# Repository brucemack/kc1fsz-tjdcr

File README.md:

Overview
========

This is my compact PCB implementation of the famous Thomas Jefferson Direct Conversion Receiver
designed by Bill Meara (N2CQR) and Dean Souleles (KK4DAS). Full documentation for the 
original rig [can be found here](https://hackaday.io/project/190327-high-schoolers-build-a-radio-receiver). This project has been discussed at length
on the excellent Solder Smoke Podcast and in a detailed series of videos that can be found
[starting here](https://www.youtube.com/watch?v=rLjxU2rMeXw). I would particularly 
encourage you to watch Dean's superb tutorial series on YouTube. 

I built this rig as part of the "Direct Conversion Challenge" issued by Bill and Dean. As
stipulated by Bill/Dean, I am resisting all temptations to modify/improve the original 
circuit. However, technically speaking this is not a *pure* TJDCR since there 
are a few departures from the recommended construction techniques and part selections. 
Importantly, I am using modern construction techniques including a commercial PCB (single board), SMD 
components (mostly 0805), and the most compact layout I could come up with. My KiCad model is provided
here for anyone who wants to experiment with it.

A huge thanks to Scott KQ4AOP for creating and sending me the tuning form 
needed to build the PTO! You also need a brass 1/4-20 bolt around 2.5" long and two 1/4-20 nuts.

Here's a demo video of the working rig:

Here's the KiCad rendering of my board.  The part reference numbers are correct
in this picture:

Here's what the raw PCB it looks like in real life. *The part reference numbers didn't 
match Bill/Dean's schematic in this version of the board* so don't get confused.  The KiCad model was later updated 
to fix this and the 2025-03 board has the correct reference numbers.

Here's the populated board:

And the full rig:

> [!IMPORTANT]  
> I know the purists may raise objections, so I would like to emphasize the value
> of building the TJDCR rig from Bill/Dean's exact specifications *first* before getting into 
> modifications including (but not limited to) PCBs and SMDs. The main point of the TJDCR
> project is to learn the process of building from scratch, and using a commercially
> fabricated PCB
> somewhat defeats that purpose. I've built DCR rigs a few times (as well as several SSB transceivers) using traditional Manhattan/Ugly (aka Beauty) 
> style so I'm trying to do something a bit different for fun. That being said, we are 
> moving into a new world where many components of value to radio homebrewers are not 
> available in through-hole packages. I would encourage everyone get over their
> fears of surface-mount parts, buy a decent headband magnifier, and start practicing 
> SMD-homebrew. I've found that by modifying the stock IPC-7351 0805 footprints provided in
> KiCad to 
> extend the pads outward 0.5mm or so you can use a normal soldering iron with a fine tip with 
> no problems.

Once the testing is complete I will make the PCB/BOM available for anyone who wants
to try building it in this style.

My [KiCAD schematic is here](https://github.com/brucemack/kc1fsz-tjdcr/blob/main/hw/tjdcr-1/plots/tjdcr-1.pdf) if you want to have a look. I've tried to use the official TJDCR part reference numbers
as much as possible.

Modification Notes
==================

This will probably get me into trouble, but I've deviated in a few places. I believe 
I've maintained the spirit of the original circuit. :grin:

* This is a single board design, whereas Bill/Dean recommend 4 boards to promote modularity.
You will note that I've silk-screened borders around the 4 modules on my board to 
emphasize the modularity of the original design. I have included test points on the 
PCB and I assemble/test the circuit in the recommended modules to simplify debug.
* I'm using ceramic non-polarized capacitors in some places where Bill/Dean used
polarized electrolytic caps.
* I'm not using the recommended silver/mica caps in my oscillator, primarily because
of size constraints. The first iteration of the build used NP0 caps and stability looked
pretty good. I strongly suspect that the compact "hardened" PCB eliminates some of the variability 
experienced in the Manhattan/Ugly construction so oscillator stability may be less of an 
issue. I'm doing some more experiments and will provide a write-up on my findings later.
* I am using T37-6/FT37-43 toroids where Bill/Dean used T50-6/FT50-43. This requires 
thinner wire and a great deal of winding patience. I think the board can physically handle the T50s 
if necessary. 
* I did not put in a trimmer for the top coupling capacitor in the band-pass filter. I'm 
comfortable with a cut-and-try approach on that component given how it impacts the shape
of the filter. Trimmers on the shunt caps are critical given the variability in the 
toroidal inductors.
* I am using Schottky diodes in the mixer since those were in the original TJDCR rig. I noticed
a later change to the 1N4148 switching diode, but I have not made that change yet.
* Note the "LO Option" connector on the board, which is not in the original 
schematic.  Normally the two pins on this connector
should be jumpered together, but those wanting to inject external VFOs may want to 
open this connection and attach the external frequency source to pin 1. This 
is also a good place to connect a frequency counter or to bridge the VFO to the 
companion transmitter module.
* There are a few extra parts (C40-C41, R40-R41) in the schematic to support a frequency offset 
feature that is described in SSDRA (page 218 figure 4). This is used to drive 
a companion CW transmitter module. Don't plug in C40 when you 
are building the stock TJDCR.

Layout Notes
============

* The space under the frequency-determining components of the VFO has been
cleared on all layers. I've read in a few places that this improves VFO 
stability by removing the large (temperature-variable) capacitor that is 
formed between the PCB copper layers.
* Via fencing is used throughout the board to isolate the VFO and the audio
amplifier from everything else.
* THe power/ground connections are intentionally placed close to the power
stage of the audio amplifier to keep these relatively large currents away
from the earlier stages.

Tools
=====

I am using KiCAD V9 for the schematic capture and PCB layout.

Current Areas of Experimentation
================================

* The first iteration used a 4-layer PCB stackup since that provides the best
RF performance. As it turns out, there is very little routed on the bottom layer and 
the +9V routing is pretty simple. Plus, at 7 MHz a lot of this probably doesn't matter. I am 
going to create a 2-layer version of the layout to shave a 
few dollars and see if this makes any measurable difference. The 4-layer boards cost $1.40
each so we're not talking about a big difference here. 2-layer boards are also more easily
made by the fabs in the US. Unfortunately, I've not found an onshore fab that can do 4 layers as
quickly/cheaply as the offshore providers, which brings up a number of geopolitical issues. (Side
note: Thomas Jefferson was a strident global free-trade advocate.)
* The initial form-factor uses what I call a "half PCB": 100mm x 35mm.
That's half of the 100mm x 70mm size that cheap copper-clad PCB stock usually comes in.
I'm thinking of reworking the layout a bit to get into the more squarish 90mm x 50mm form-factor 
that is needed to fit into a Peppermint Altoids tin. Major QRP street cred possible here.
* I also like the super-small binocular BN43-2402 ferrite cores and will be testing
those on the mixer stage in the next iteration.
* I have a companion CW transmitter module I call "James Madison" which I will 
document later.

Bill Of Materials (2025-03 Version)
===================================

This parts list is provided for informational purposes. I didn't provide part numbers for a lot of the
generic components because I have a collection of those on hand. I like the 0805 SMD resistor and 
capacitor "books" since they contain anything you could ever want. The more unique parts can be
ordered from [DigiKey](http://www.digikey.com) using the part numbers provided. The audio transformer is a Mouser-only part.
The 2.54mm headers are cut from a long header strip.

This parts list follows the Bill/Dean component reference numbering scheme.

| Reference	| Value	| Notes |
| --------- | ----- | ----- |
| C1,C2 | 660p | NP0 Ceramic 0805 |
| C3 | 130p | NP0 Ceramic 0805 |
| C4,C5,C6,C7,C21,C41 | 0.1u | Generic Ceramic 0805 |
| C8,C14 | 10u | Generic Ceramic 0805 |
| C9,C11,C13 | 470u 10V | Tantalum in 7343 package, polarized (EX: Kyocera TPSE477K010R0100) |
| C10,C12,C15 | 47u | Generic Ceramic 0805 |
| C16 | 0.47u | Generic Ceramic 0805 |
| C17 | 33u | Generic Ceramic 0805 |
| C18,C19 | 150p | NP0 Ceramic 0805 |
| C20 | 10p | NP0 Ceramic 0805 |
| C40,C181,C191 | 6.5-30pF Trimmer | Manufacturer package (EX: EW Electronics GKG30086-05) |
| D1 | 8.2V 250mW Zener | SOT23-3 package (EX: onsemi BZX84C8V2LT1G) |
| D25,D34 | Schottky Diode Array | Pay attention to polarity, SOT23-3 package (EX: Diotec Semi BAT54S) |
| J1 | Antenna (50 ohms) | SMA connector female through-hole (EX: Amphenol 901-144-8RFX) |
| J2 | Tuning | Generic 2.54mm header |
| J3 | Power | Generic 2.54mm header | 
| J4 | LO Option | Generic 2.54mm header |
| J5 | Volume | Generic 2.54mm header |
| J6 | Speaker | Generic 2.54mm header |
| J7 | TX Offset | Generic 2.54mm header |
| L2 | 10u | 0805 package (EX: Taiyo Yuden LBR2012T100K) |
| L11 | 100u | 0805 package (EX: TDK MLZ2012N101LT000) |
| Q1,Q3,Q5,Q40 | NPN Transistor 3904 | SOT23-3 package (EX: onsemi MMBT3904LT1G) |
| Q2 | JFET Transistor J310 | SOT23-3 package (EX: onsemi SMMBFJ310LT3G) |
| Q4 | NPN Transistor 3904 | Generic TO-92 package |
| R1,R2 | 10k | Generic 0805 |
| R3 | 3.3k | Generic 0805 |
| R4,R6,R14 | 100R | Generic 0805 |
| R5 | 100k | Generic 0805 |
| R7 | 47R |	Generic 0805 |
| R8,R12,R16 | 14.7k | Generic 0805 |
| R9,R13,R17 | 4.7k | Generic 0805 |
| R10,R18 | 1k | Generic 0805 |
| R11,R19 | 470R | Generic 0805 |
| R20 | 220R | Generic 0805 |
| R40 | 47k | Generic 0805 |
| R41 | 2.2k | Generic 0805 |
| T1 | 5:28 Toroid transformer | Wound on T37-6 toroid, #28 wire |
| T2 | 5:28 Toroid transformer | Wound on T37-6 toroid, #28 wire |
| T3 | 1:1:1 Toroid transformer (trifilar) | Wound on FT37-43 toroid, #28 wire |
| T4 | 1:1:1 Toroid transformer (trifilar) | Wound on FT37-43 toroid, #28 wire |
| T5 | 8R:1k audio transformer| EX: Mouser 42TL013-RC |

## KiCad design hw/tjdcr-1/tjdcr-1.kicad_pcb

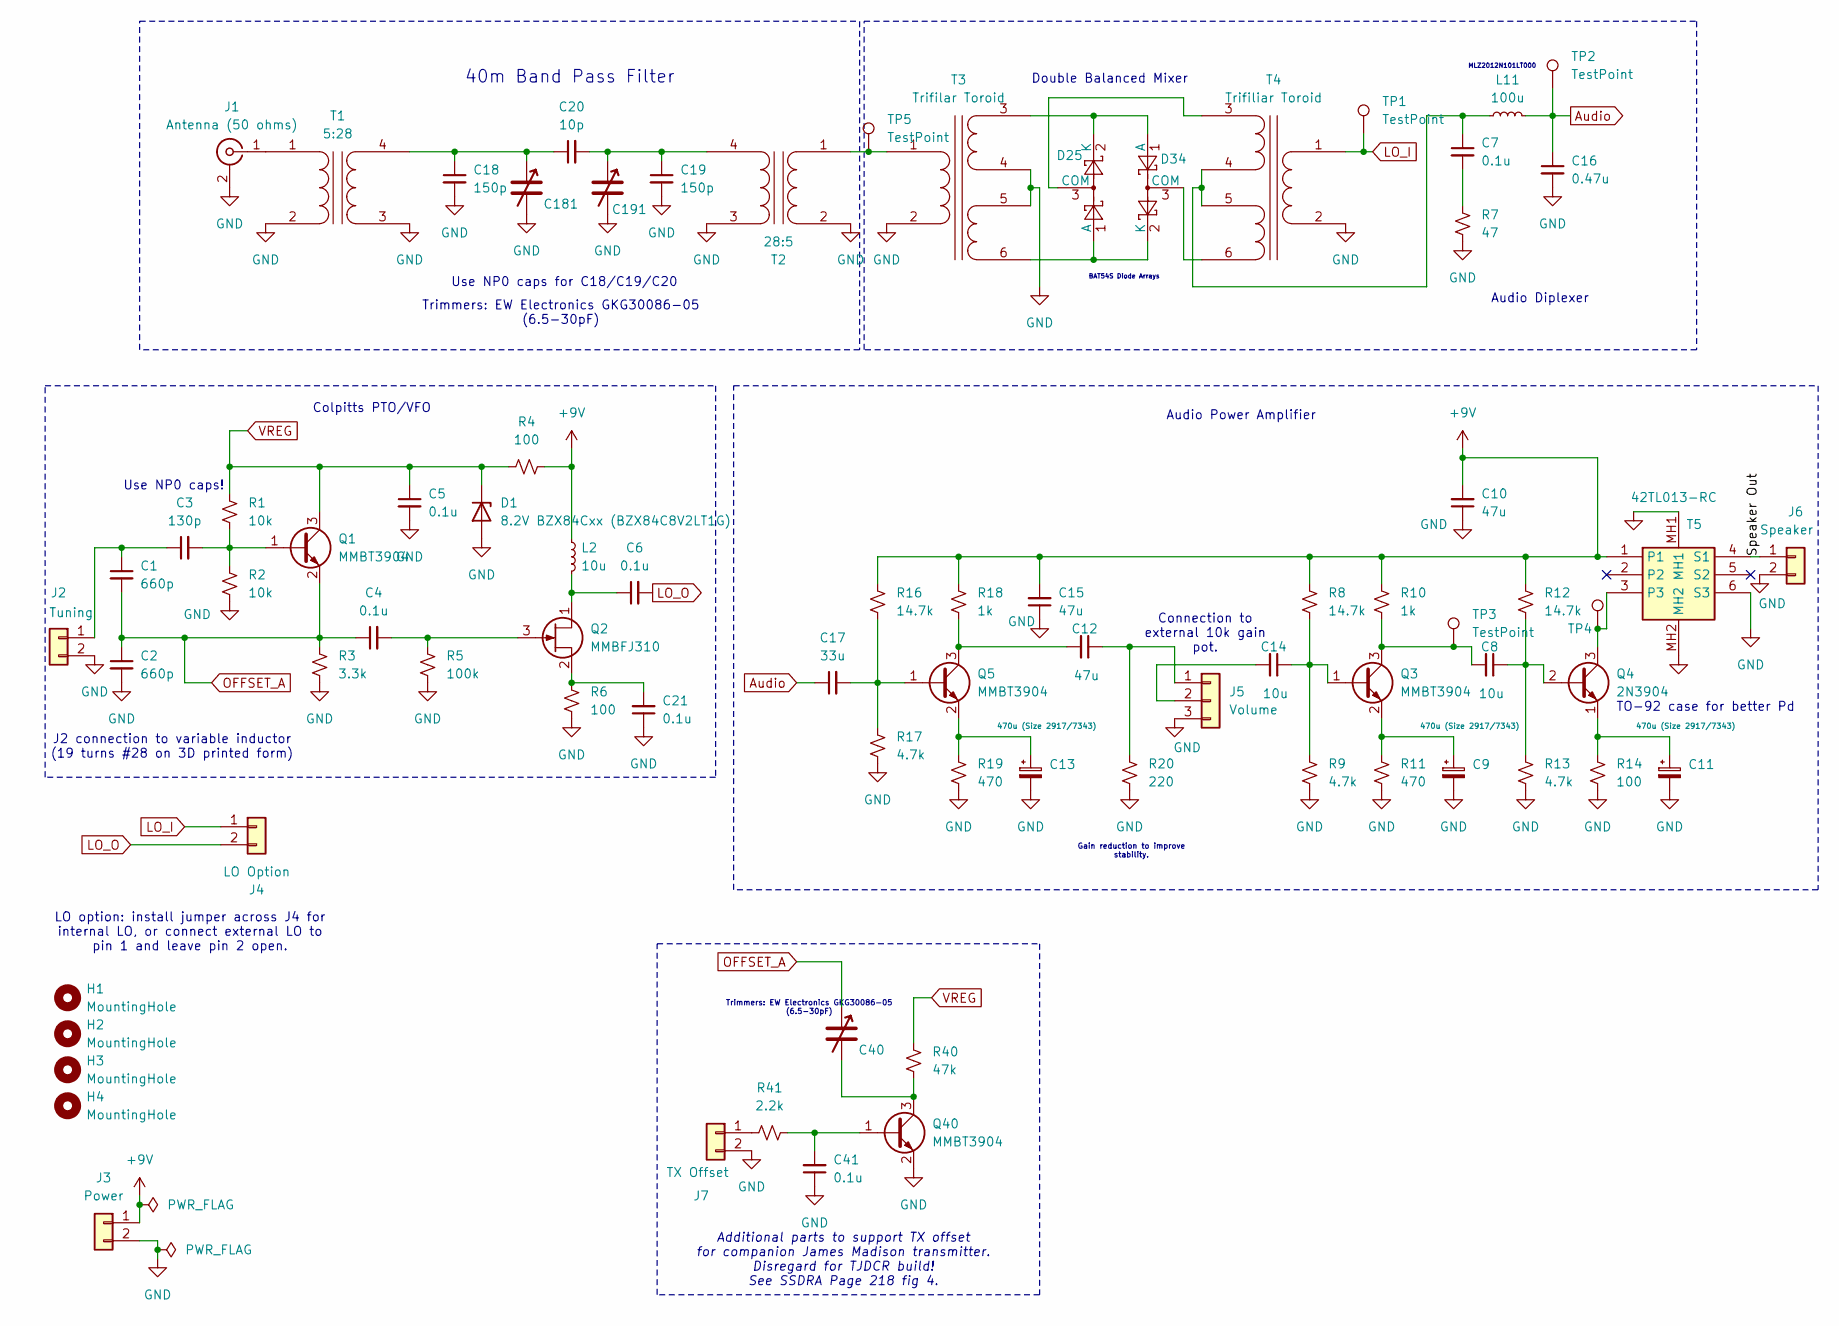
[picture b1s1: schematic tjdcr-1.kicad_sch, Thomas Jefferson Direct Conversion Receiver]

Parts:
C1, C2: 660p; C_0805_2012Metric_Pad1.18x1.45mm_HandSolder
C3: 130p; C_0805_2012Metric_Pad1.18x1.45mm_HandSolder
C4, C5, C6, C7, C21, C41: 0.1u; C_0805_2012Metric_Pad1.18x1.45mm_HandSolder
C8, C14: 10u; C_0805_2012Metric_Pad1.18x1.45mm_HandSolder
C9, C11, C13: 470u (Size 2917/7343); CP_EIA-7343
C10, C12, C15: 47u; C_0805_2012Metric_Pad1.18x1.45mm_HandSolder
C16: 0.47u; C_0805_2012Metric_Pad1.18x1.45mm_HandSolder
C17: 33u; C_0805_2012Metric_Pad1.18x1.45mm_HandSolder
C18, C19: 150p; C_0805_2012Metric_Pad1.18x1.45mm_HandSolder
C20: 10p; C_0805_2012Metric_Pad1.18x1.45mm_HandSolder
C40, C181, C191: C_Variable; VCAP_GKG30086-05_SGM-L
D1: 8.2V BZX84Cxx (BZX84C8V2LT1G); SOT-23
D25, D34: BAT54S; SOT-23
H1, H2, H3, H4: MountingHole; MountingHole_2.5mm
J1: Antenna (50 ohms); PinHeader_1x02_P2.54mm_Vertical
J2: Tuning; PinHeader_1x02_P2.54mm_Vertical
J3: Power; PinHeader_1x02_P2.54mm_Vertical
J4: LO Option; PinHeader_1x02_P2.54mm_Vertical
J5: Volume; PinHeader_1x03_P2.54mm_Vertical
J6: Speaker; PinHeader_1x02_P2.54mm_Vertical
J7: TX Offset; PinHeader_1x02_P2.54mm_Vertical
L2: 10u; L_0805_2012Metric_Pad1.15x1.40mm_HandSolder
L11: 100u; L_1210_3225Metric_Pad1.42x2.65mm_HandSolder
Q1, Q3, Q5, Q40: MMBT3904; SOT-23
Q2: MMBFJ310; SOT-23
Q4: 2N3904; TO-92_Inline
R1, R2: 10k; R_0805_2012Metric_Pad1.20x1.40mm_HandSolder
R3: 3.3k; R_0805_2012Metric_Pad1.20x1.40mm_HandSolder
R4, R6, R14: 100; R_0805_2012Metric_Pad1.20x1.40mm_HandSolder
R5: 100k; R_0805_2012Metric_Pad1.20x1.40mm_HandSolder
R7: 47; R_0805_2012Metric_Pad1.20x1.40mm_HandSolder
R8, R12, R16: 14.7k; R_0805_2012Metric_Pad1.20x1.40mm_HandSolder
R9, R13, R17: 4.7k; R_0805_2012Metric_Pad1.20x1.40mm_HandSolder
R10, R18: 1k; R_0805_2012Metric_Pad1.20x1.40mm_HandSolder
R11, R19: 470; R_0805_2012Metric_Pad1.20x1.40mm_HandSolder
R20: 220; R_0805_2012Metric_Pad1.20x1.40mm_HandSolder
R40: 47k; R_0805_2012Metric_Pad1.20x1.40mm_HandSolder
R41: 2.2k; R_0805_2012Metric_Pad1.20x1.40mm_HandSolder
T1: 5:28; Transformer_Toroid_Horizontal_D9.0mm_Amidon-T30
T2: 28:5; Transformer_Toroid_Horizontal_D9.0mm_Amidon-T30
T3: Trifilar Toroid; SmallTrifilar
T4: Trifiliar Toroid; SmallTrifilar
T5: 42TL013-RC; 42TL013RC; Mouser Part Number 42TL013-RC
TP1, TP2, TP3, TP4, TP5: TestPoint; TestPoint_Pad_1.5x1.5mm

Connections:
+9V: C10.2, C15.2, J3.1, L2.1, R4.2, R8.1, R10.1, R12.1, R16.1, R18.1, T5.1
/Speaker Out: J6.1, T5.4 (S1)
Audio: C16.1, C17.1, L11.2, TP2.1
GND: C2.2, C5.2, C9.2, C10.1, C11.2, C13.2, C15.1, C16.2, C18.2, C19.2, C21.1, C41.1, C181.2, C191.2, D1.1 (A), J1.2 (Ext), J2.2, J3.2, J5.3, J6.2, J7.2, Q40.2 (E), R2.2, R3.2, R5.2, R6.2, R7.2, R9.2, R11.2, R13.2, R14.2, R17.2, R19.2, R20.2, T1.2 (AB), T1.3 (SA), T2.2 (AB), T2.3 (SA), T3.2 (AB), T3.4 (SB), T3.5 (SC), T4.2 (AB), T5.6 (S3), T5.MH1, T5.MH2
LO_I: J4.1, T4.1 (AA), TP1.1
LO_O: C6.2, J4.2
unnamed: C7.2, R7.1
unnamed: D25.1 (A), D34.2 (K), T3.6 (SD)
unnamed: D25.3 (COM), T4.3 (SA)
unnamed: D25.2 (K), D34.1 (A), T3.3 (SA)
unnamed: D34.3 (COM), T4.6 (SD)
unnamed: J1.1 (In), T1.1 (AA)
unnamed: C1.1, C3.1, J2.1
unnamed: C12.1, J5.1, R20.1
unnamed: C14.2, J5.2
unnamed: J7.1, R41.1
unnamed: C3.2, Q1.1 (B), R1.2, R2.1
unnamed: C6.1, L2.2, Q2.1 (D)
unnamed: C4.2, Q2.3 (G), R5.1
unnamed: C21.2, Q2.2 (S), R6.1
unnamed: C14.1, Q3.1 (B), R8.2, R9.1
unnamed: C8.2, Q3.3 (C), R10.2, TP3.1
unnamed: C9.1, Q3.2 (E), R11.1
unnamed: C8.1, Q4.2 (B), R12.2, R13.1
unnamed: Q4.3 (C), T5.3, TP4.1
unnamed: C11.1, Q4.1 (E), R14.1
unnamed: C17.2, Q5.1 (B), R16.2, R17.1
unnamed: C12.2, Q5.3 (C), R18.2
unnamed: C13.1, Q5.2 (E), R19.1
unnamed: C41.2, Q40.1 (B), R41.2
unnamed: C40.2, Q40.3 (C), R40.2
unnamed: C18.1, C20.1, C181.1, T1.4 (SB)
unnamed: T2.1 (AA), T3.1 (AA), TP5.1
unnamed: C19.1, C20.2, C191.1, T2.4 (SB)
unnamed: C7.1, L11.1, T4.4 (SB), T4.5 (SC)
OFFSET_A: C1.2, C2.1, C4.1, C40.1, Q1.2 (E), R3.1
VREG: C5.1, D1.3 (K), Q1.3 (C), R1.1, R4.1, R40.1

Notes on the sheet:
Trimmers: EW Electronics GKG30086-05 (6.5-30pF)
Audio Diplexer
MLZ2012N101LT000
40m Band Pass Filter
Additional parts to support TX offset for companion James Madison transmitter. Disregard for TJDCR build! See SSDRA Page 218 fig 4.
LO option: install jumper across J4 for internal LO, or connect external LO to pin 1 and leave pin 2 open.
BAT54S Diode Arrays
J2 connection to variable inductor (19 turns #28 on 3D printed form)
Use NP0 caps for C18/C19/C20
Colpitts PTO/VFO
Connection to external 10k gain pot.
Double Balanced Mixer
Use NP0 caps!
Gain reduction to improve stability.
Audio Power Amplifier
TO-92 case for better Pd

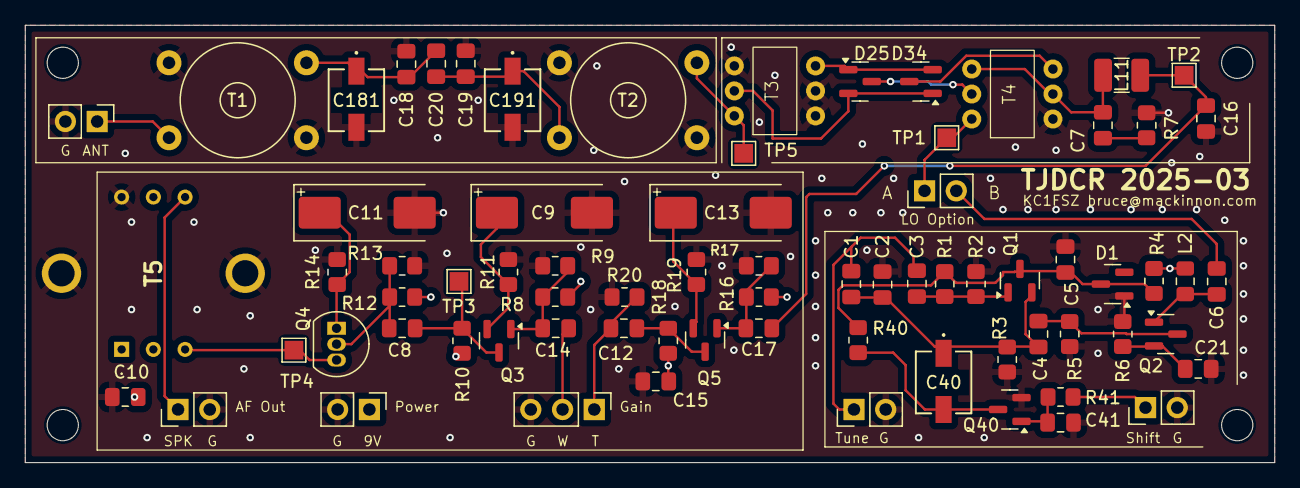
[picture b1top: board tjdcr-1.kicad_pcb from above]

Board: 4 copper layers, 100.0 x 35.0 mm, 78 parts (0 on the bottom side), 37 nets.

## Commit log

2025-02-21 Working
2025-02-21 Layout is progressing
2025-02-21 All wires connected
2025-02-22 Checkpoint before adding variable caps
2025-02-22 Checkpoint after audio transformer change, preparing for flip of audio amp
2025-02-22 Checkpoint after audio amp reverse
2025-02-22 Ready to send this version to fab
2025-02-22 Corrected schematic error
2025-02-22 Sent to JLCPCB
2025-02-23 Changed reference numbers
2025-02-24 Added TX offset to schematic
2025-02-24 Docs
2025-03-07 PCB for 2025-03 board
2025-03-07 Added BOM to documentation, testing 2025-03 board
2025-03-11 Fixed L2 component

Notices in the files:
hw/tjdcr-1/tjdcr-1.kicad_pcb:
Copyright (C) Bruce MacKinnon, 2025
